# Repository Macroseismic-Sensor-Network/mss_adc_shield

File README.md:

# MSS ADC Shield

This repository contains the [KiCad](https://www.kicad.org/) design files of the MSS ADC Shield for the [Raspberry Pi](https://www.raspberrypi.org). A PDF of the schematic can be found in the *pdf* folder and the PCB layout files are available in Gerber format in the *gerber* folder.

# License
Copyright 2021, Mertl Research GmbH.
Built upon a design by Daniel Frank.
Licensed under the [CERN-OHL-S v2](https://ohwr.org/cern_ohl_s_v2.txt).

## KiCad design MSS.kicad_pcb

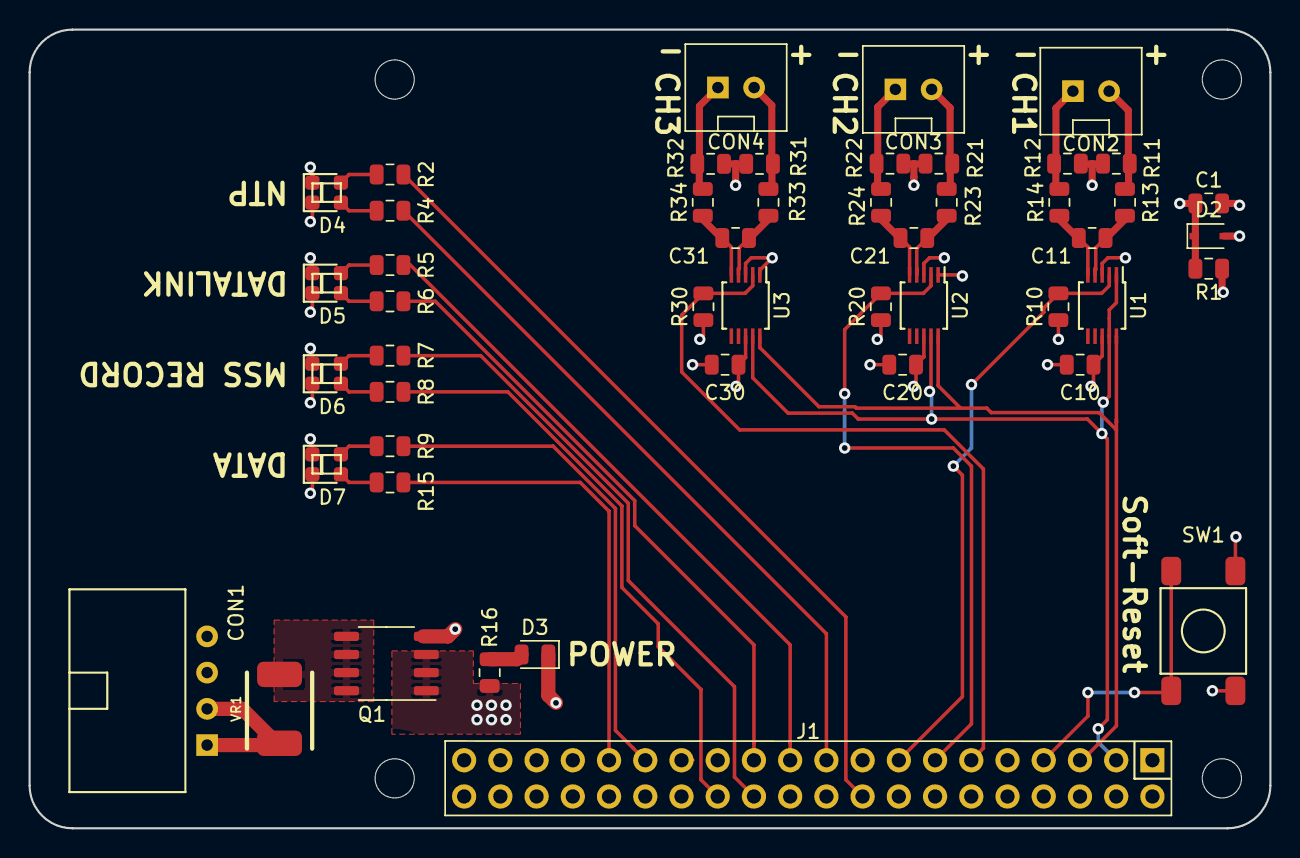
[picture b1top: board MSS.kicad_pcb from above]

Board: 4 copper layers, 87.0 x 56.0 mm, 53 parts (0 on the bottom side), 41 nets.

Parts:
C1, C10, C11, C20, C21, C30, C31: 1uF; C_0805_2012Metric
CON1: IPL1-104-01-L-S-RE1
CON2, CON3, CON4: IPL1-102-01-L-S
D2: BZT52C2V0S-7-F; D_SOD-323
D3: 150080VS75000; LED_0805_2012Metric
D4, D5, D6, D7: 150080RV54050; WL-SBCD-0805
J1: RPi; RPi_Socket_Strip_Straight_2x20_Pitch2.54mm
MH1, MH2, MH3, MH4: MountingHole_2.75mm_M2.5
Q1: FDS6576; ON_751EB_SOIC-8
R1, R10, R20, R30: 1k8; R_0805_2012Metric
R2, R4, R5, R6, R7, R8, R9, R15: 680; R_0805_2012Metric
R11, R12, R21, R22, R31, R32: 100k; R_0805_2012Metric
R13, R14, R23, R24, R33, R34: 6k2; R_0805_2012Metric
R16: 1k5; R_0805_2012Metric
SW1: 430152043836; Push_Button_6x6
U1, U2, U3: ADS1114; TSSOP-10_3x3mm_P0.5mm
VR1: 1812L110/33MR; PF1812L

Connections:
+3V3: C10.2, C20.2, C30.2, J1.1, R1.1, R10.1, R20.1, R30.1, U1.8, U2.1, U2.8, U3.8
+5V: J1.2, J1.4, Q1.1, Q1.2, Q1.3, R16.2
/CH1+: CON2.2, R11.2, R13.2
/CH1-: CON2.1, R12.2, R14.2
/CH2+: CON3.2, R21.2, R23.2
/CH2-: CON3.1, R22.2, R24.2
/CH3+: CON4.2, R31.2, R33.2
/CH3-: CON4.1, R32.2, R34.2
/LED1_G: J1.19, R4.1
/LED1_R: J1.18, R2.1
/LED2_G: J1.23, R6.1
/LED2_R: J1.21, R5.1
/LED3_G: J1.26, R8.1
/LED3_R: J1.24, R7.1
/LED4_G: J1.31, R15.1
/LED4_R: J1.29, R9.1
GND: C1.2, C10.1, C20.1, C30.1, CON1.3, CON1.4, D2.2, D3.1, D4.1, D4.2, D5.1, D5.2, D6.1, D6.2, D7.1, D7.2, J1.6, J1.9, J1.14, J1.20, J1.25, J1.30, J1.34, J1.39, Q1.4, SW1.1, U1.3, U2.3, U3.1, U3.3
unnamed: C11.1, R13.1, U1.4
unnamed: C11.2, R14.1, U1.5
unnamed: C21.1, R23.1, U2.4
unnamed: C21.2, R24.1, U2.5
unnamed: C31.1, R33.1, U3.4
unnamed: C31.2, R34.1, U3.5
unnamed: CON1.1, CON1.2, VR1.1
unnamed: D3.2, R16.1
unnamed: D4.3, R4.2
unnamed: D4.4, R2.2
unnamed: D5.3, R6.2
unnamed: D5.4, R5.2
unnamed: D6.3, R8.2
unnamed: D6.4, R7.2
unnamed: D7.3, R15.2
unnamed: D7.4, R9.2
unnamed: J1.7, SW1.2
unnamed: Q1.5, Q1.6, Q1.7, Q1.8, VR1.2
RDY_1: J1.15, R10.2, U1.2
RDY_2: J1.13, R20.2, U2.2
RDY_3: J1.11, R30.2, U3.2
SCL: J1.5, U1.10, U2.10, U3.10
SDA: J1.3, U1.1, U1.9, U2.9, U3.9
VAA: C1.1, D2.1, R1.2, R11.1, R12.1, R21.1, R22.1, R31.1, R32.1

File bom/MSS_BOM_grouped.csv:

Source:,/home/stefan/01_gtd/04_aktuelleProjekte/2019-13_mss_outreach_netidee/02_meilensteine/20200909_mss_produktion/03_adc_platine/MSS.sch
Date:,Mo 28 Sep 2020 15:02:26 CEST
Tool:,Eeschema 5.1.6-c6e7f7d~87~ubuntu18.04.1
Number of components:,49
ref,value,quantity,manufacturer,manufacturer part number,package,description,footprint,library,part name
"C1,C10,C11,C20,C21,C30,C31",1uF,7,Samsung Electro-Mechanics,CL21B105KBFNNNF,0805,"Samsung, CL, SMD MLCC, Vielschicht Keramikkondensator X7R, 1μF ±10% / 50V dc, Gehäuse 0805 (2012M)",Capacitor_SMD:C_0805_2012Metric,symbols,C_Small
CON1,IPL1-104-01-L-S-RE1,1,Samtec,IPL1-104-01-L-S-RE1,IPL1-104-01-L-S-RE1,"Samtec IPL1 single row, 4 pins, right angle, raised",footprints:IPL1-104-01-L-S-RE1,symbols,IPL1-104-01-L-S-RE1
"CON2,CON3,CON4",IPL1-102-01-L-S,3,Samtec,IPL1-102-01-L-S-RE1,IPL1-102-01-L-S-RE1,"Samtec IPL1 single row, 2 pins, straight",footprints:IPL1-102-01-L-S,symbols,IPL1-102-01-L-S
D2,BZT52C2V0S-7-F,1,Diodes Incorporated,BZT52C2V0S-7-F,SOD-323,"Zener Diode, 2.0V, 200mW, 5%",Diode_SMD:D_SOD-323,Device,D_Zener_Small_ALT
D3,150080VS75000,1,Würth Elektronik,150080VS75000,0805,"WL-SMCW SMT Mono-color Chip LED Waterclear, green",LED_SMD:LED_0805_2012Metric,Device,LED
"D4,D5,D6,D7",150080RV54050,4,Würth Elektronik,150080RV54050,WL-SBCD-0805,"WL-SBCD SMT Bi-color Chip LED Diffused, red - green",footprints:WL-SBCD-0805,symbols,150080RV54050
J1,RPi,1,Samtec,ESQ-120-44-L-D,20x2 2.54mm pitch,"Elevated Socket Strip, 2.54mm Pitch",footprints:RPi_Socket_Strip_Straight_2x20_Pitch2.54mm,Connector_Generic,Conn_02x20_Odd_Even
Q1,FDS6576,1,ON Semiconductor,FDS6576,SO-8,"P-Channel MOSFET, 20V DS, 11A, +/-12V GS, 14 mOhm",footprints:ON_751EB_SOIC-8,symbols,FDS6576
"R1,R10,R20,R30",1k8,4,TE Connectivity,CRG0805F1K8,0805,"TE Connectivity CRG SMD Dickschichtwiderstand, 1,8kΩ ±1% 0,125W, 0805",Resistor_SMD:R_0805_2012Metric,symbols,R_Small
"R2,R4,R5,R6,R7,R8,R9,R15",680,8,TE Connectivity,CRG0805F680R,0805,"TE Connectivity CRG SMD Dickschichtwiderstand, 680Ω ±1% 0,125W, 0805",Resistor_SMD:R_0805_2012Metric,symbols,R_Small
"R11,R12,R21,R22,R31,R32",100k,6,TE Connectivity,CRG0805F100K,0805,"TE Connectivity CRG SMD Dickschichtwiderstand, 100kΩ ±1% 0,125W, 0805",Resistor_SMD:R_0805_2012Metric,symbols,R_Small
"R13,R14,R23,R24,R33,R34",6k2,6,TE Connectivity,CRCW08056K20FKEA,0805,"TE Connectivity CRG SMD Dickschichtwiderstand, 6,2kΩ ±1% 0,125W, 0805",Resistor_SMD:R_0805_2012Metric,symbols,R_Small
R16,1k5,1,TE Connectivity,CRG0805F1K5,0805,"TE Connectivity CRG SMD Dickschichtwiderstand, 1,5kΩ ±1% 0,125W, 0805",Resistor_SMD:R_0805_2012Metric,symbols,R_Small
SW1,430152043836,1,Würth Elektronik,430152043836,6mm x 6mm,WS-TASV SMT Tact Switch 6x6 mm,footprints:Push_Button_6x6,Switch,SW_Push
"U1,U2,U3",ADS1114,3,Texas Instruments,ADS1114IDGST,TSSOP10,"ADS111x Ultra-Small, Low-Power, I 2 C-Compatible, 860-SPS, 16-Bit ADCsWith Internal Reference, Oscillator, and Programmable Comparator",Package_SO:TSSOP-10_3x3mm_P0.5mm,symbols,ADS1114
VR1,1812L110/33MR,1,Littlefuse,1812L110/33MR,PF1812L,"Littelfuse 1.1A Surface Mount Resettable Fuse, 33 V dc",footprints:PF1812L,symbols,Varistance

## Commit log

2021-04-28 Initial commit.
2021-04-28 Restored the symbols library. It got lost somehow.
2021-04-28 Removed a temporary file from the repository.
2021-04-28 Added temporary Kicad files.
2021-04-28 Added the CERN-OHL-S v2 license.
2021-04-28 Added the Github Readme file.
2021-04-28 Added the schematic pdf and gerber files of the PCB.
2021-04-28 Added a short description.
2021-04-28 Fixed the license link.
2021-04-28 Renamed the license file.

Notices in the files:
MSS.kicad_pcb:
Licensed unter CERN-OHL-v2
